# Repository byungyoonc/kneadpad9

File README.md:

# 꾹꾹이패드9
야옹전자 매크로패드 프로젝트: 3x3 직결 매크로패드입니다.

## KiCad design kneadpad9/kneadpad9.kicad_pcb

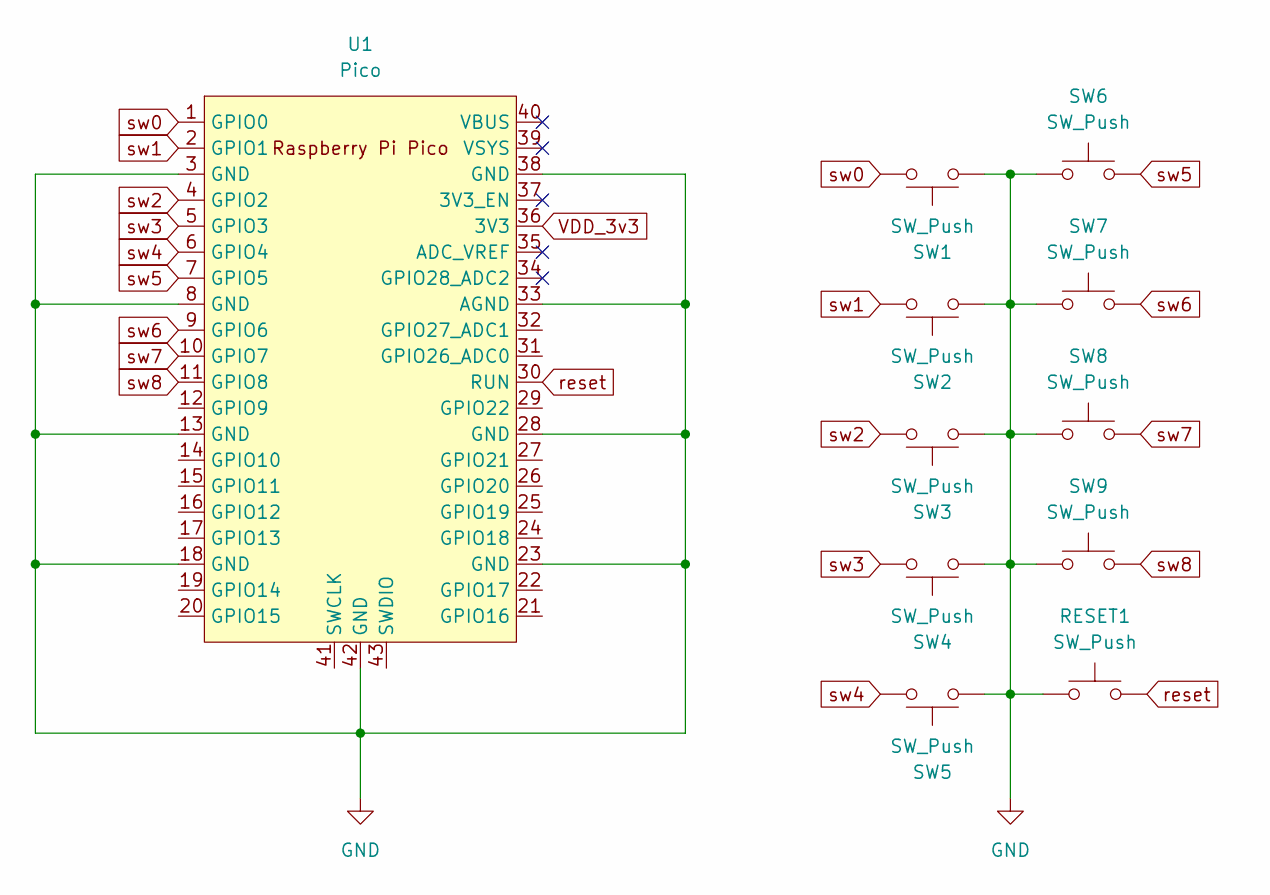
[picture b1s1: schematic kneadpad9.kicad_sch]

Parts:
RESET1: SW_Push; SW_SPST_CK_RS282G05A3
SW1, SW2, SW3, SW4, SW5, SW6, SW7, SW8, SW9: SW_Push; MX-Hotswap-1U
U1: Pico; RPi_Pico_SMD_TH

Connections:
GND: RESET1.1, SW1.1, SW2.1, SW3.1, SW4.1, SW5.1, SW6.1, SW7.1, SW8.1, SW9.1, U1.3 (GND), U1.8 (GND), U1.13 (GND), U1.18 (GND), U1.23 (GND), U1.28 (GND), U1.33 (AGND), U1.38 (GND), U1.42 (GND); also elsewhere on the board
VDD_3v3: U1.36 (3V3)
reset: RESET1.2, U1.30 (RUN); also elsewhere on the board
sw0: SW1.2, U1.1 (GPIO0)
sw1: SW2.2, U1.2 (GPIO1)
sw2: SW3.2, U1.4 (GPIO2)
sw3: SW4.2, U1.5 (GPIO3)
sw4: SW5.2, U1.6 (GPIO4)
sw5: SW6.2, U1.7 (GPIO5)
sw6: SW7.2, U1.9 (GPIO6)
sw7: SW8.2, U1.10 (GPIO7)
sw8: SW9.2, U1.11 (GPIO8)

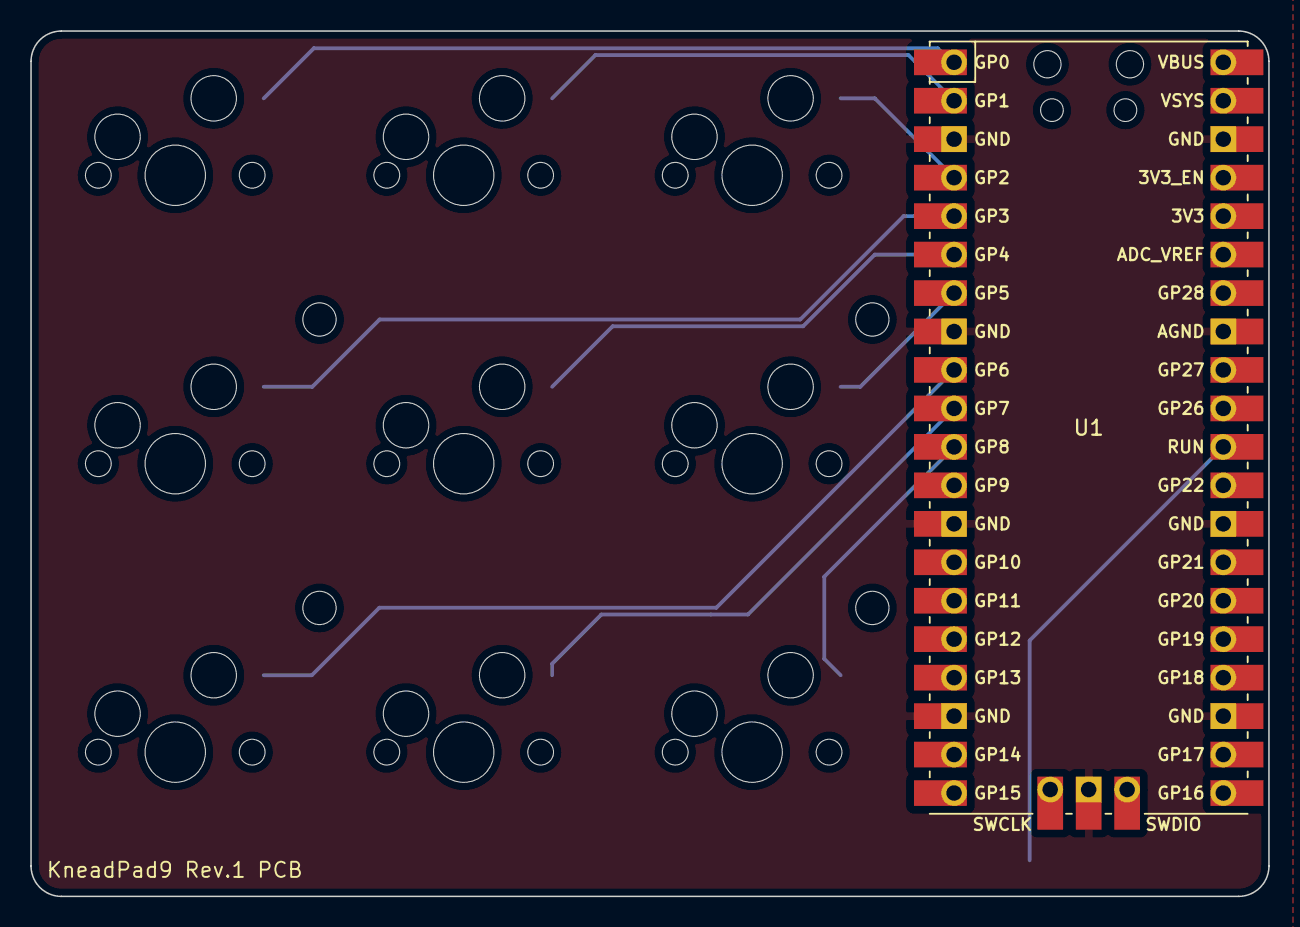
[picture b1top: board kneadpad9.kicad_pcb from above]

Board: 2 copper layers, 81.8 x 57.2 mm, 11 parts (1 on the bottom side), 11 nets.

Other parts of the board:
RESET: SW_Push; SW_SPST_CK_RS282G05A3

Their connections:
GND: RESET.1; also elsewhere on the board
reset: RESET.2; also elsewhere on the board

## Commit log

2023-01-17 Create LICENSE
2023-01-17 Add empty KiCad project
2023-01-17 Add submodules
2023-01-17 Update library tables
2023-01-17 Wrote PCB/Schematic
2023-01-18 Change keypad layout
2023-01-26 Change project name
2023-01-26 Add M2 mounting holes for backplate
2023-01-26 Update edge cuts for better alignment
2023-01-27 Added bottom and top plates, added silkscreen label
2023-01-27 Change gerber output settings
2023-01-27 Ignore output files in Git
2023-02-06 added logo on bottom plate
2023-02-06 Add placeholder label for JLC order
2023-02-19 Add via configuration
2023-03-06 Add Via firmware
